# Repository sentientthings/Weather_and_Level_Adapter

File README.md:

# Weather_and_Level_Adapter
Weather and Level Adapter for the Sentient Things IoT Node

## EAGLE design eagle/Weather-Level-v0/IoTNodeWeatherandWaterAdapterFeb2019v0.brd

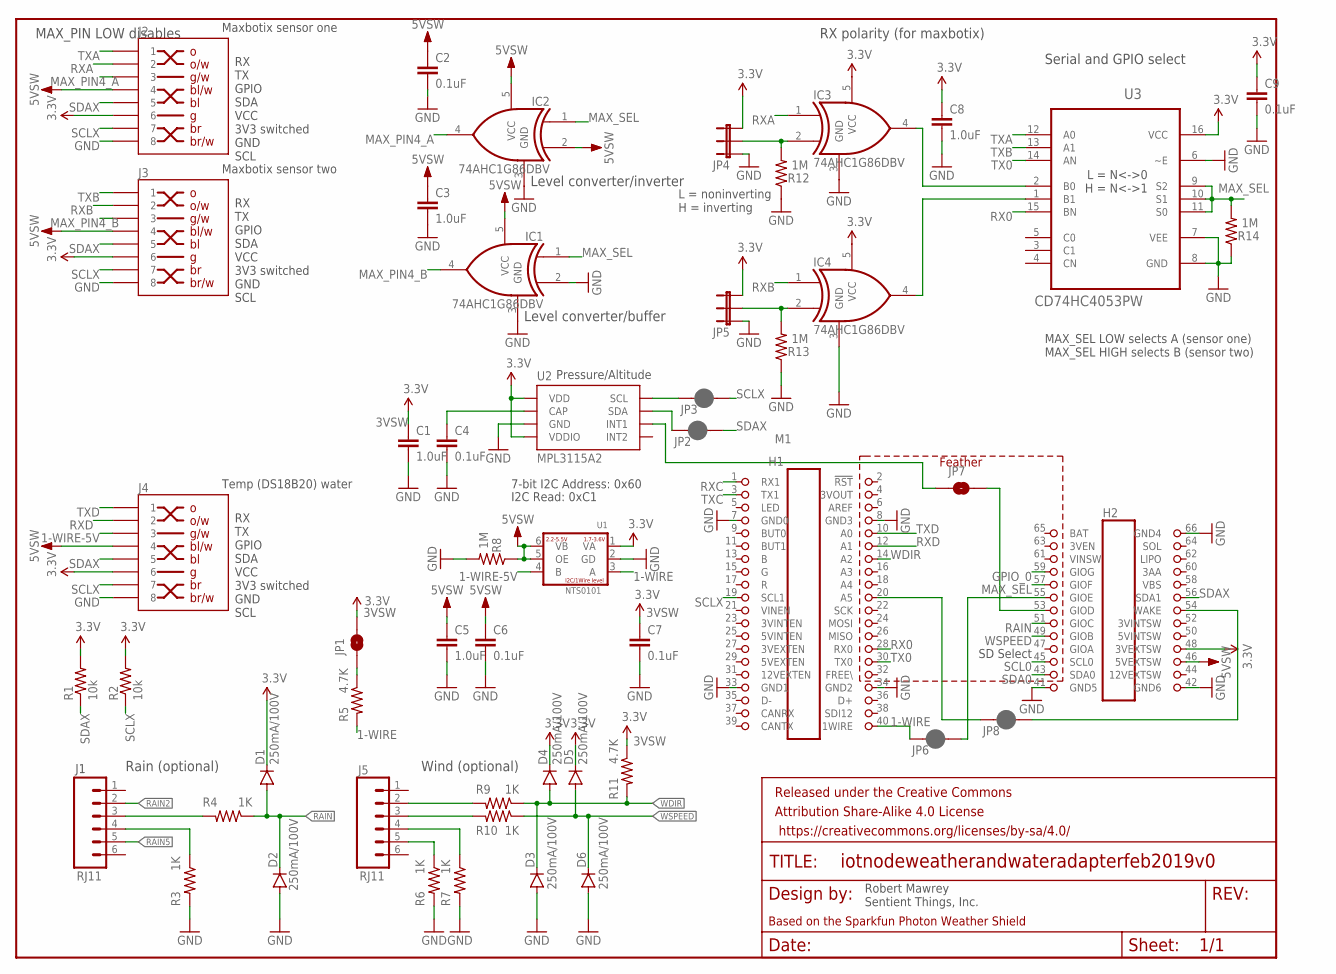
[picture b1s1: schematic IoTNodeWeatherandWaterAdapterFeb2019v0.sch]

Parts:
C1, C3, C5, C8: 1.0uF; 0603-CAP; PARTNO CC0603KRX7R8BB105
C2, C4, C6, C7, C9: 0.1uF; 0603-CAP; PARTNO C1608X5R1H104K080AA
D1, D2, D3, D4, D5, D6: 250mA/100V; SOD-323; PARTNO BAS16J,135
FRAME1: FRAME-LETTER; CREATIVE_COMMONS; PARTNO DNP
H1: IOTNODE2X20PLACEMENT; 2X20PLACEMENT
H2: IOTNODE2X13PLACEMENT; 2X13PLACEMENT
IC1, IC2, IC3, IC4: 74AHC1G86DBV; SOT23-5; PARTNO SN74AHC1G86DBVR
J1, J5: RJ11; RJ11-6; PARTNO 5555165-1
J2, J3, J4: RJ45-8-UP; RJHSE-5080; PARTNO RJHSE-5080
JP1: JUMPER-PAD-2-NOYES_SILK; PAD-JUMPER-2-NO_YES_SILK; PARTNO DNP
JP2, JP3, JP6, JP8: JUMPER-SMT_2_NC_PASTE_NO-SILK; SMT-JUMPER_2_NC_PASTE_NO-SILK; PARTNO DNP
JP4, JP5: JUMPER-3LOCK; 1X03_LOCK; PARTNO 68000-103HLF
JP7: JUMPER-SMT_2_NO_NO-SILK; SMT-JUMPER_2_NO_NO-SILK; PARTNO DNP
M1: IOTNODEFEATHERWING; PARTNO DNP
R1, R2: 10k; 0603-RES; PARTNO ERJ-3GEYJ103V
R3, R4, R6, R7, R9, R10: 1K; 0603-RES; PARTNO RC0603JR-071KL
R5, R11: 4.7K; 0603-RES; PARTNO RC0603JR-074K7L
R8, R12, R13, R14: 1M; 0603; PARTNO RC0603FR-071ML
U1: NTS0101; SOT363_PHILIPS; PARTNO NTS0101GW,125
U2: MPL3115A2; LGA-8-5X3; PARTNO MPL3115A2
U3: CD74HC4053PW; SOP65P640X120-16N; PARTNO 74HC4053PW,118

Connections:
1-WIRE: JP6.2, M1.40 (1WIRE), R5.2, U1.3 (A)
1-WIRE-5V: J4.3, U1.4 (B)
3VSW: C1.1, C7.1, C8.1, C9.1, D1.C, D4.C, D5.C, IC3.5 (VCC), IC4.5 (VCC), J2.6, J3.6, J4.6, JP1.2, JP4.3, JP5.3, M1.48 (3VEXTSW), R1.2, R2.2, R11.1, U1.1 (VA), U2.1 (VDD), U2.4 (VDDIO), U3.16 (VCC)
5VSW: C2.1, C3.1, C5.1, C6.1, IC1.5 (VCC), IC2.2 (I1), IC2.5 (VCC), J2.4, J3.4, J4.4, M1.46 (5VEXTSW), R8.1, U1.5 (OE), U1.6 (VB)
GND: C1.2, C2.2, C3.2, C4.2, C5.2, C6.2, C7.2, C8.2, C9.2, D2.A, D3.A, D6.A, IC1.2 (I1), IC1.3 (GND), IC2.3 (GND), IC3.3 (GND), IC4.3 (GND), J2.8, J3.8, J4.8, JP4.1, JP5.1, M1.7 (GND0), M1.8 (GND3), M1.33 (GND1), M1.34 (GND2), M1.41 (GND5), M1.42 (GND6), M1.66 (GND4), R3.2, R6.2, R7.2, R8.2, R12.1, R13.1, R14.1, U1.2 (GD), U2.3 (GND), U3.6 (~E), U3.7 (VEE), U3.8 (GND)
GPIO_0: M1.59 (GIOG)
MAX_PIN4_A: IC2.4 (O), J2.3
MAX_PIN4_B: IC1.4 (O), J3.3
MAX_SEL: IC1.1 (I0), IC2.1 (I0), M1.57 (GIOF), R14.2, U3.9 (S2), U3.10 (S1), U3.11 (S0)
unnamed: J5.3, R10.2
unnamed: J5.2, R9.2
unnamed: J1.3, R4.2
unnamed: C4.1, U2.2 (CAP)
unnamed: JP6.1, M1.55 (GIOE)
unnamed: JP7.1, U2.6 (INT1)
unnamed: J1.4, R3.1
unnamed: J5.5, R6.1
unnamed: J5.4, R7.1
unnamed: IC3.4 (O), U3.2 (B0)
unnamed: IC4.4 (O), U3.1 (B1)
unnamed: JP8.2, M1.20 (A5)
unnamed: JP7.2, M1.53 (GIOD)
unnamed: IC4.2 (I1), JP5.2, R13.2
unnamed: JP3.2, U2.8 (SCL)
unnamed: JP8.1, M1.54 (WAKE)
unnamed: JP2.2, U2.7 (SDA)
unnamed: JP1.1, R5.1
RA: IC3.2 (I1), JP4.2, R12.2
RAIN: D1.A, D2.C, M1.51 (GIOC), R4.1
RAIN2: J1.2
RAIN5: J1.5
RX0: M1.28 (RX0), U3.15 (BN)
RXA: IC3.1 (I0), J2.2
RXB: IC4.1 (I0), J3.2
RXC: M1.1 (RX1)
RXD: J4.2, M1.12 (A1)
SCL0: M1.45 (SCL0)
SCLX: J2.7, J3.7, J4.7, JP3.1, M1.19 (SCL1), R2.1
SDA0: M1.43 (SDA0)
SDAX: J2.5, J3.5, J4.5, JP2.1, M1.56 (SDA1), R1.1
TX0: M1.30 (TX0), U3.14 (AN)
TXA: J2.1, U3.12 (A0)
TXB: J3.1, U3.13 (A1)
TXC: M1.3 (TX1)
TXD: J4.1, M1.10 (A0)
WDIR: D3.C, D4.A, M1.14 (A2), R9.1, R11.2
WSPEED: D5.A, D6.C, M1.49 (GIOB), R10.1

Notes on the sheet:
Wind (optional)
Rain (optional)
Based on the Sparkfun Photon Weather Shield
RX polarity (for maxbotix)
Maxbotix sensor one
Maxbotix sensor two
Temp (DS18B20) water
RX TX GPIO SDA VCC 3V3 switched GND SCL
Level converter/buffer
Serial and GPIO select
L = N<->0 H = N<->1
L = noninverting H = inverting
SD Select
I2C Read: 0xC1
7-bit I2C Address: 0x60
Pressure/Altitude
MAX_SEL LOW selects A (sensor one) MAX_SEL HIGH selects B (sensor two)
Level converter/inverter
MAX_PIN LOW disables
Robert Mawrey Sentient Things, Inc.

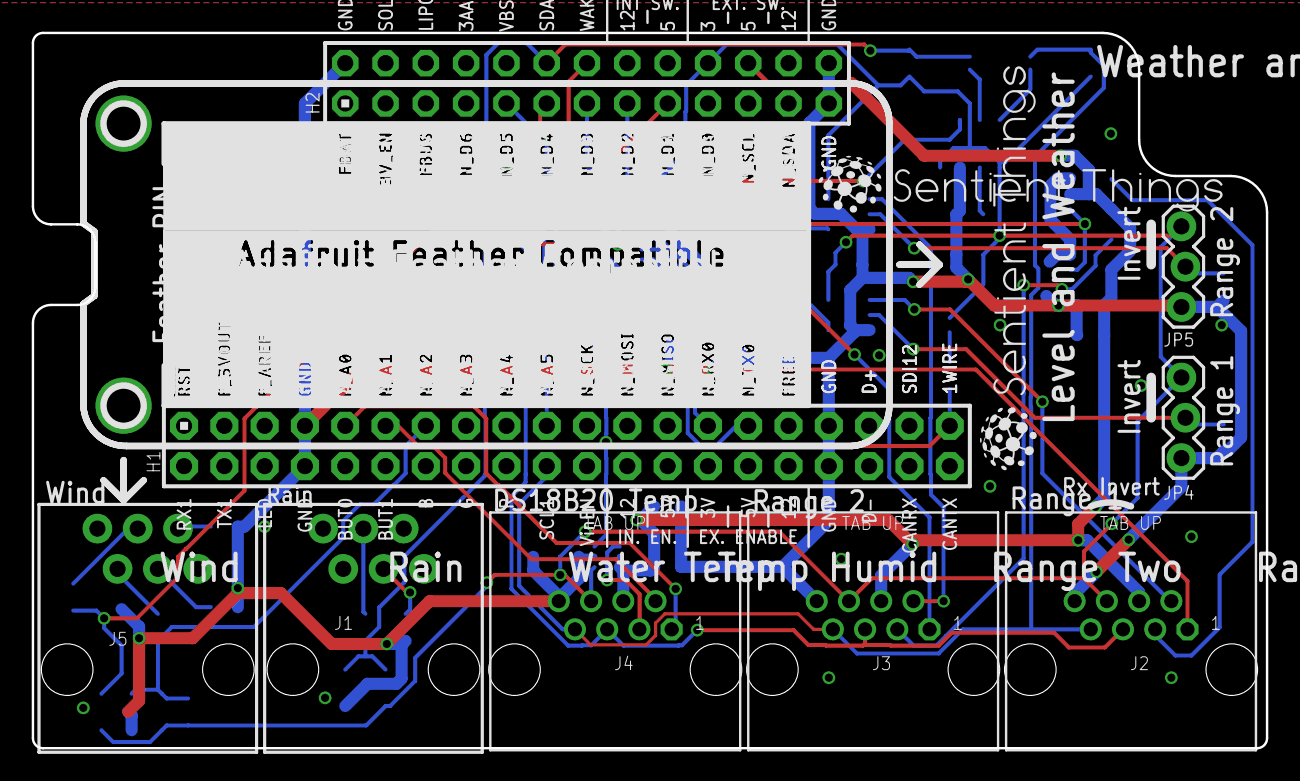
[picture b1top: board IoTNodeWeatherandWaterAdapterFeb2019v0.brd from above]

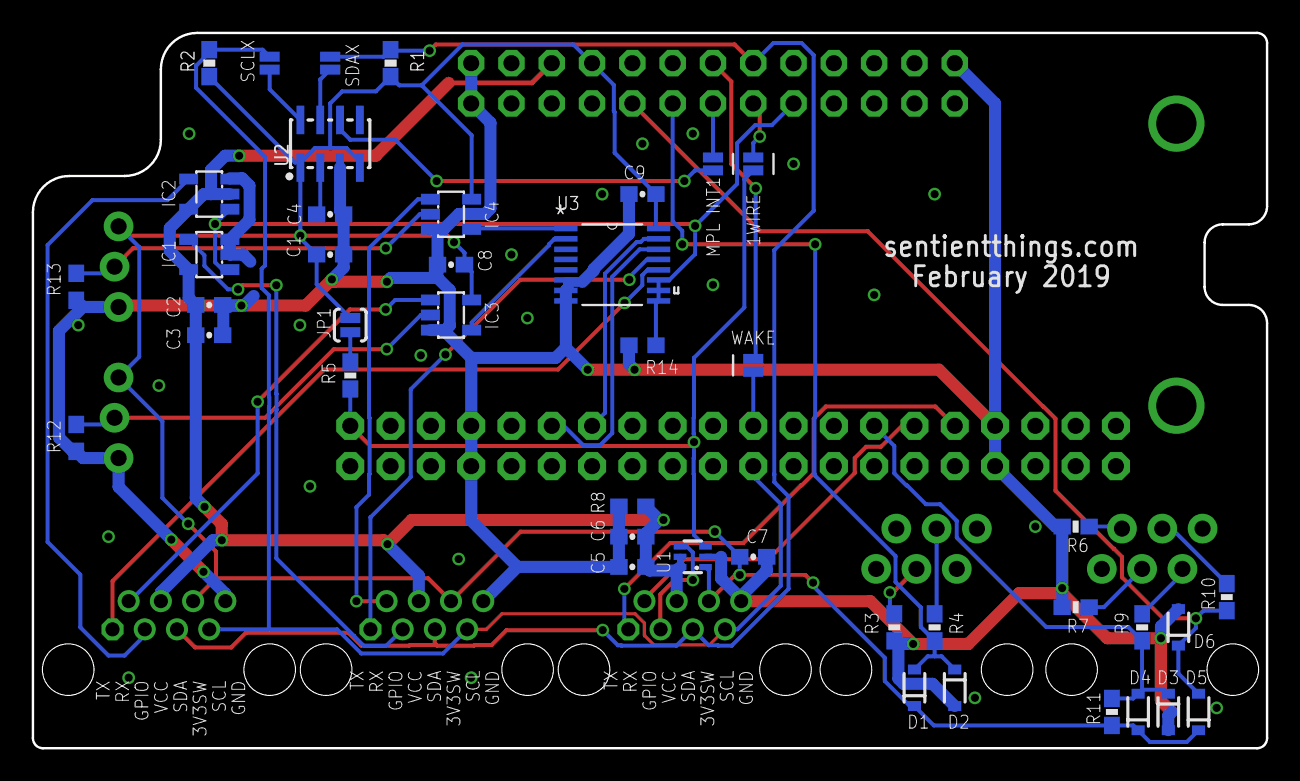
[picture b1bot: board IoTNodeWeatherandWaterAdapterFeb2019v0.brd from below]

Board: 2 copper layers, 77.8 x 45.1 mm, 56 parts (42 on the bottom side), 40 nets.

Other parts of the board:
U$1: SENTIENT_TSILK
U$2: SENTIENT_THINGS
U$3: IOTNODEINSIDESILK

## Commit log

2019-05-13 Create test
2019-05-13 Add libraries
2019-05-13 Add project properties for source
2019-05-13 Add source
2019-05-13 Minor edit to remove old comment
2019-05-14 Update IoTNodeWeatherLevelGlobals to include P1
2019-05-14 Update IoTNodeWeatherLevelGlobals
2019-05-14 Updated to correctly include P1 platform_ID=8
2019-05-14 Correcting IoTNodeWeatherLevelGlobals=0.0.12
2019-05-14 Update firstRunTest variable
2019-05-21 Updated Readme files
2019-05-21 PCB files
2019-05-21 license
2019-10-02 Updated to use FramI2C=0.0.11
2019-10-15 Fixed rain bug
2019-10-17 Update for 622 char publish
    Updated library to work with 622 char Particle.publish. Assumes Particle version works with 622 chars.

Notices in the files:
parts and their libraries:
SparkFun-DiscreteSemi: Licensing: Creative Commons ShareAlike 4.0 International - https://creativecommons.org/licenses/by-sa/4.0
Mawrey: Released under the Creative Commons Attribution Share-Alike 4.0 License
Mawrey: https://creativecommons.org/licenses/by-sa/4.0
